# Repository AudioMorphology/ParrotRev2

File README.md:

# Parrot

##  Overview

Parrot is a 12hp Eurorack digital delay powered by a Raspberry Pi Pico microcontroller.

The objective is to provide a CD-Quality audio delay  / reverb effect, with a reasonably 
low BOM count

It utilises an 8Mb x 8-Bit (64mBit) PSRAM Memory chip (the AP6404L), and the whole of
this is treated as a 2Mb x 32-Bit audio buffer. This means that we can wrap the read and 
write pointers  with a simple logical &. 

2Mb x 32-Bit is 1Mb at 32-Bit Stereo. At a 48kHz sample rate, this gives a maximum delay 
time of 1,048,576 / 48,000 = 21.84 seconds 

The ADC and DAC ICs communicate over the i2S protocol, which is handled by custom PIO
functions.

They are actually 24-Bit devices with the data being transmitted left-justified in 32-Bit 
frames, so I am rightshifting to get 24-Bit Integers, then converting these to normalised
floats in the range -1.0 to +1.0 then, after processing it does the same in reverse before 
sending the audio data out to the DAC. 

Reading and writing to the PSRAM buffer is double-buffered using DMA calls from the I2S
interface.

It uses two PIO State machines:

PIO0 for SPI
PIO1 for I2S

The ADC and DAC utilises the low-cost and readily-available I2S modules, which have the 
advantages of already including various ancilliary components, which further reduces the
component count and complexity.

## NOTICE

This code incorporates and acknowledges the following:

### rp2040-psram Copyright © 2023 Ian Scott

rp2040-psram is a header-only library, which implements the SPI protocol using the rp2040 PIO
rather than the in-built SPI interface. This gives far better performance for PSRAM SPI peripherals

### i2s Copyright © 2022 Daniel Collins

These functions implement the I2S protocol using the rp2040 PIO. and utilise interrupt-driven
DMA double-buffering for Audio I/O.

### Elements of hardware design Copyright © 2012 Emilie Gillet (emilie.o.gillet@gmail.com)

The input and output buffer circuitry was taken directly from Clouds:
https://github.com/pichenettes/eurorack/tree/master/clouds/hardware_design/pcb

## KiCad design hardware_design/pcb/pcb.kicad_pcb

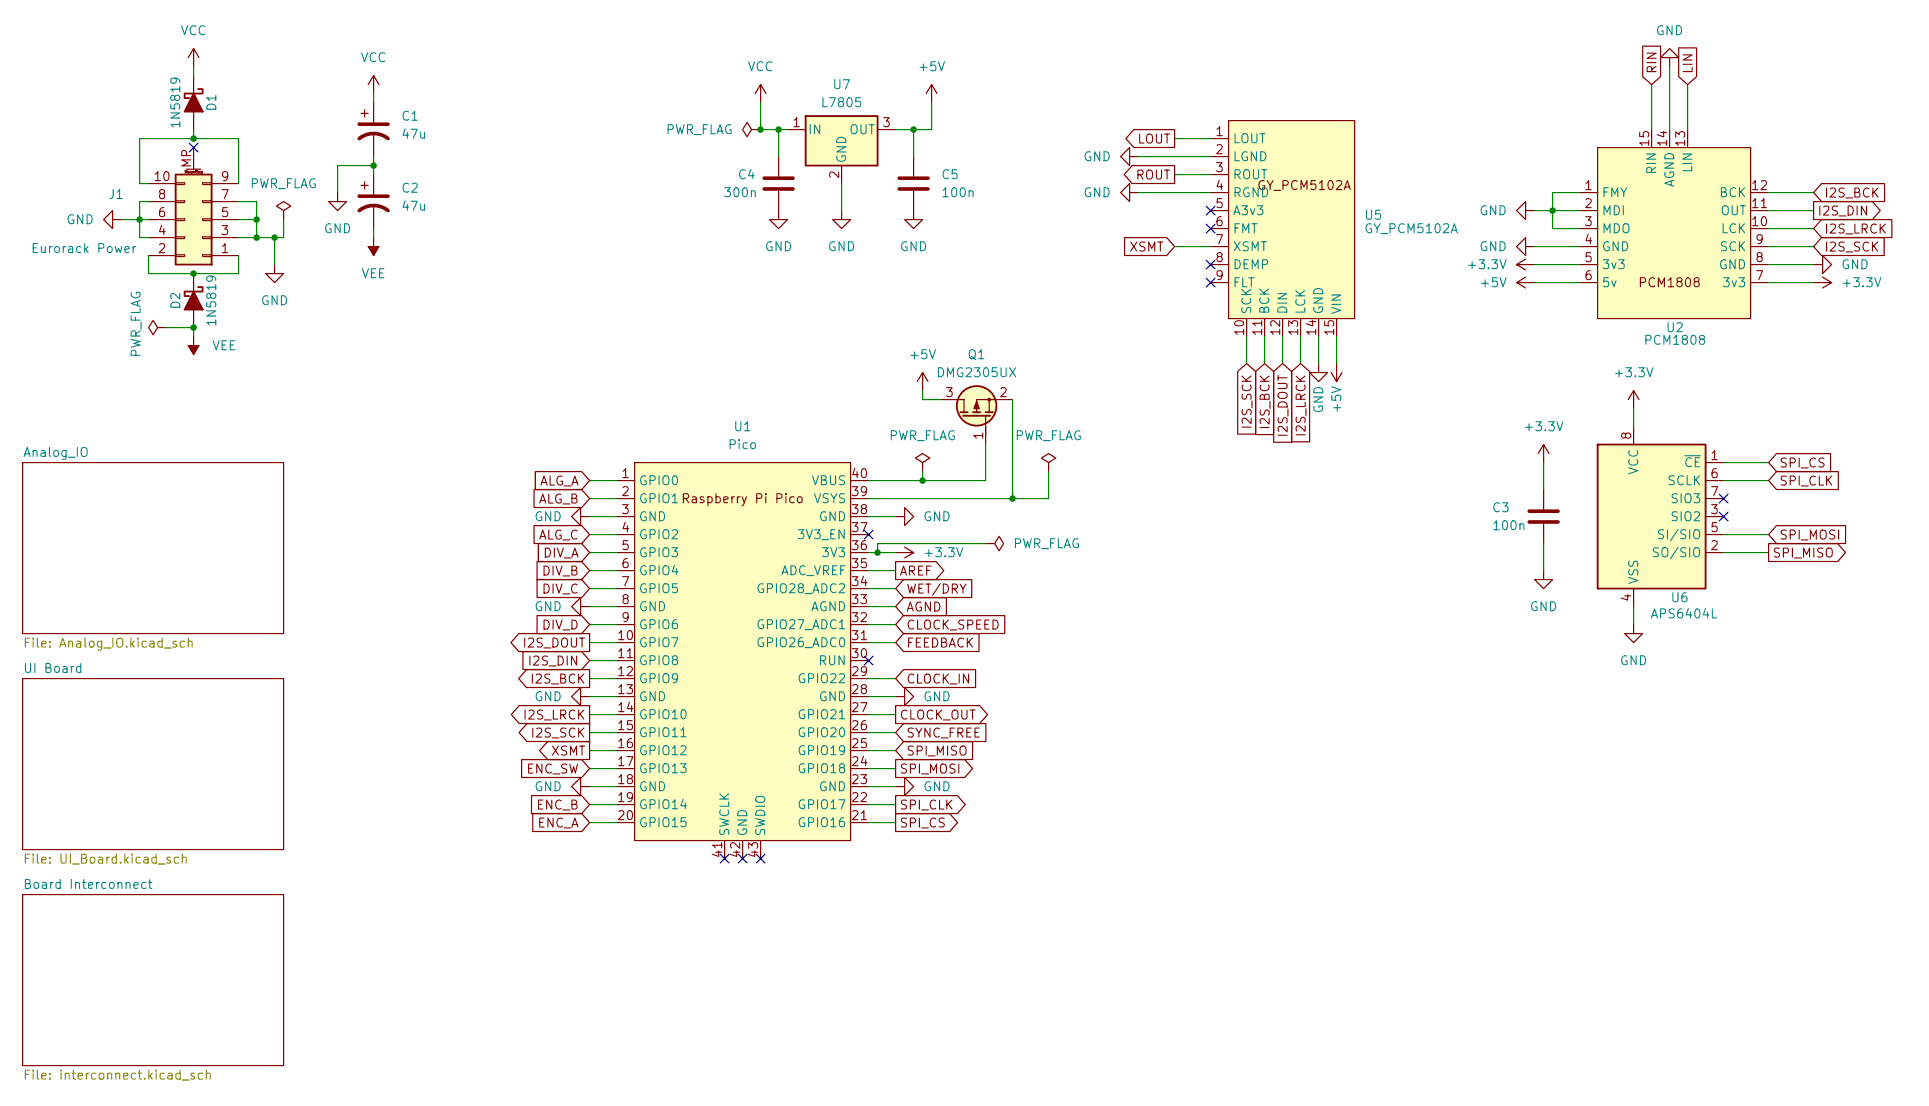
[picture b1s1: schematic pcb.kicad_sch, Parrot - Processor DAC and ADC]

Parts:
C1, C2: 47u; CP_Elec_6.3x5.8
C3, C5: 100n; C_0603_1608Metric
C4: 300n; C_0603_1608Metric
D1, D2: 1N5819; D_DO-41_SOD81_P7.62mm_Horizontal
J1: Eurorack Power; IDC-Header_2x05_P2.54mm_Vertical
Q1: DMG2305UX; SOT-23
U1: Pico; RPi_Pico_SMD_TH
U2: PCM1808
U5: GY_PCM5102A
U6: APS6404L; SOIC-8_3.9x4.9mm_P1.27mm
U7: L7805; TO-252-2 with heatsink

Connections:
+3.3V: C3.1, U1.36 (3V3), U2.5 (3v3), U2.7 (3v3), U6.8 (VCC); also elsewhere on the board
+5V: C5.1, Q1.3 (D), U2.6 (5v), U5.15 (VIN), U7.3 (OUT)
AGND: U1.33 (AGND); also elsewhere on the board
ALG_A: U1.1 (GPIO0); also elsewhere on the board
ALG_B: U1.2 (GPIO1); also elsewhere on the board
ALG_C: U1.4 (GPIO2); also elsewhere on the board
AREF: U1.35 (ADC_VREF); also elsewhere on the board
CLOCK_IN: U1.29 (GPIO22); also elsewhere on the board
CLOCK_OUT: U1.27 (GPIO21); also elsewhere on the board
CLOCK_SPEED: U1.32 (GPIO27_ADC1); also elsewhere on the board
DIV_A: U1.5 (GPIO3); also elsewhere on the board
DIV_B: U1.6 (GPIO4); also elsewhere on the board
DIV_C: U1.7 (GPIO5); also elsewhere on the board
DIV_D: U1.9 (GPIO6); also elsewhere on the board
ENC_A: U1.20 (GPIO15); also elsewhere on the board
ENC_B: U1.19 (GPIO14); also elsewhere on the board
ENC_SW: U1.17 (GPIO13); also elsewhere on the board
FEEDBACK: U1.31 (GPIO26_ADC0); also elsewhere on the board
GND: C1.2, C2.1, C3.2, C4.2, C5.2, J1.3, J1.4, J1.5, J1.6, J1.7, J1.8, U1.3 (GND), U1.8 (GND), U1.13 (GND), U1.18 (GND), U1.23 (GND), U1.28 (GND), U1.38 (GND), U2.1 (FMY), U2.2 (MDI), U2.3 (MDO), U2.4 (GND), U2.8 (GND), U2.14 (AGND), U5.2 (LGND), U5.4 (RGND), U5.14 (GND), U6.4 (VSS), U7.2 (GND); also elsewhere on the board
I2S_BCK: U1.12 (GPIO9), U2.12 (BCK), U5.11 (BCK)
I2S_DIN: U1.11 (GPIO8), U2.11 (OUT)
I2S_DOUT: U1.10 (GPIO7), U5.12 (DIN)
I2S_LRCK: U1.14 (GPIO10), U2.10 (LCK), U5.13 (LCK)
I2S_SCK: U1.15 (GPIO11), U2.9 (SCK), U5.10 (SCK)
LIN: U2.13 (LIN); also elsewhere on the board
LOUT: U5.1 (LOUT); also elsewhere on the board
unnamed: D1.2 (A), J1.9, J1.10
unnamed: D2.1 (K), J1.1, J1.2
unnamed: Q1.1 (G), U1.40 (VBUS)
unnamed: Q1.2 (S), U1.39 (VSYS)
RIN: U2.15 (RIN); also elsewhere on the board
ROUT: U5.3 (ROUT); also elsewhere on the board
SPI_CLK: U1.22 (GPIO17), U6.6 (SCLK)
SPI_CS: U1.21 (GPIO16), U6.1 (~CE)
SPI_MISO: U1.25 (GPIO19), U6.2 (SO/SIO)
SPI_MOSI: U1.24 (GPIO18), U6.5 (SI/SIO)
SYNC_FREE: U1.26 (GPIO20); also elsewhere on the board
VCC: C1.1, C4.1, D1.1 (K), U7.1 (IN); also elsewhere on the board
VEE: C2.2, D2.2 (A); also elsewhere on the board
WET/DRY: U1.34 (GPIO28_ADC2); also elsewhere on the board
XSMT: U1.16 (GPIO12), U5.7 (XSMT)

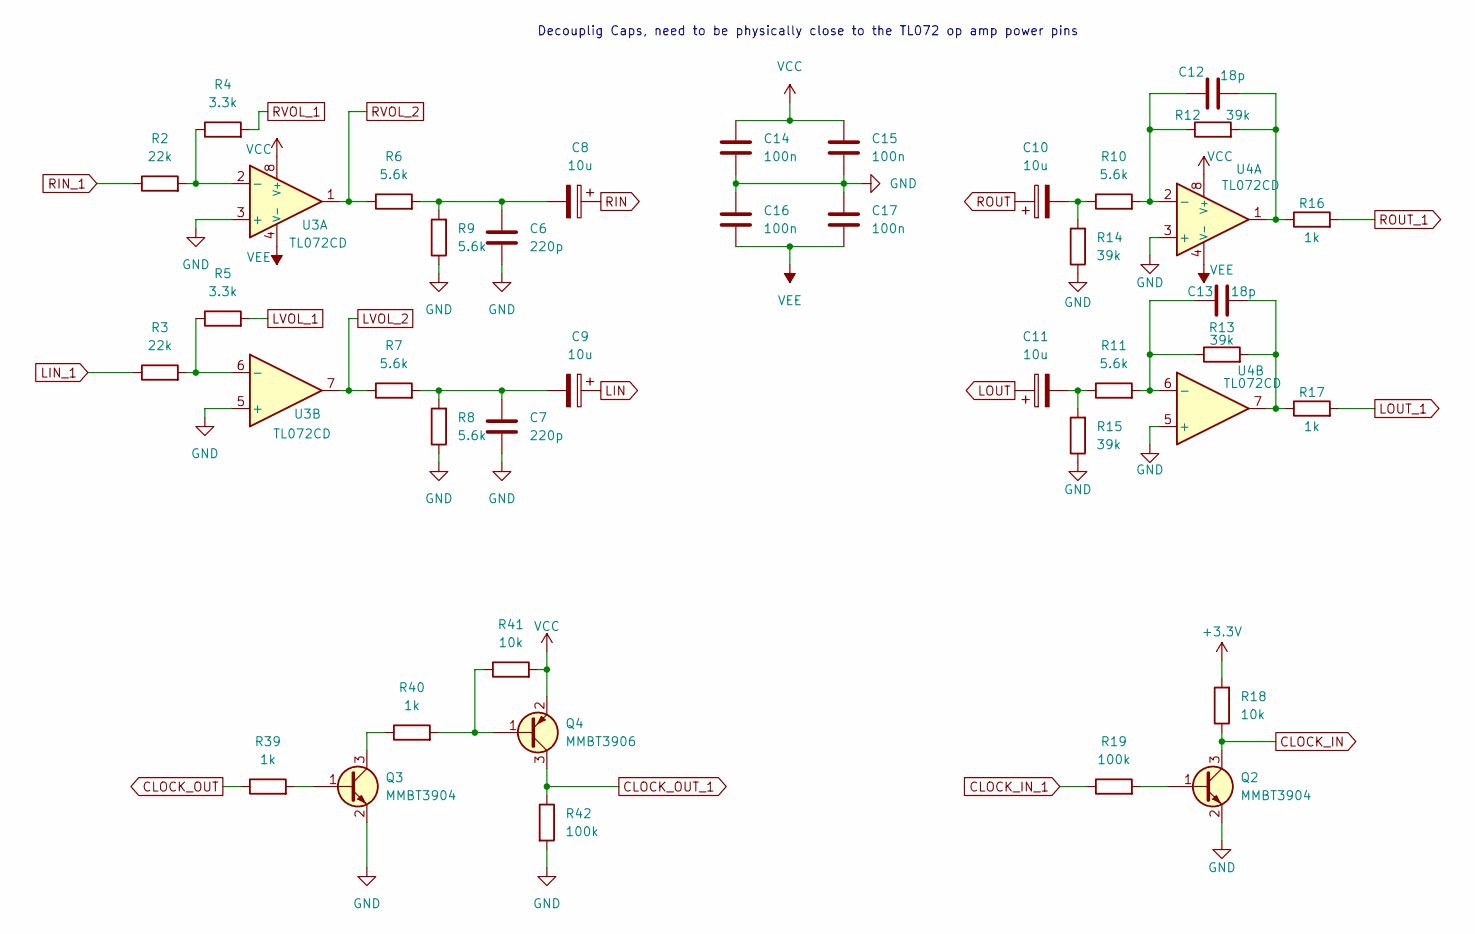
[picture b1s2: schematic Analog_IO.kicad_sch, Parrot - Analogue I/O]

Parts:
C6, C7: 220p; C_0603_1608Metric
C8, C9, C10, C11: 10u; CP_Elec_6.3x5.8
C12, C13: 18p; C_0603_1608Metric
C14, C15, C16, C17: 100n; C_0603_1608Metric
Q2, Q3: MMBT3904; SOT-23
Q4: MMBT3906; SOT-23
R2, R3: 22k; R_0603_1608Metric_Pad1.05x0.95mm_HandSolder
R4, R5: 3.3k; R_0603_1608Metric_Pad1.05x0.95mm_HandSolder
R6, R7, R8, R9, R10, R11: 5.6k; R_0603_1608Metric_Pad1.05x0.95mm_HandSolder
R12, R13, R14, R15: 39k; R_0603_1608Metric_Pad1.05x0.95mm_HandSolder
R16, R17, R39, R40: 1k; R_0603_1608Metric_Pad1.05x0.95mm_HandSolder
R18, R41: 10k; R_0603_1608Metric_Pad1.05x0.95mm_HandSolder
R19, R42: 100k; R_0603_1608Metric_Pad1.05x0.95mm_HandSolder
U3, U4: TL072CD; SO-8_3.9x4.9mm_P1.27mm

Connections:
+3.3V: R18.2; also elsewhere on the board
CLOCK_IN: Q2.3 (C), R18.1; also elsewhere on the board
CLOCK_IN_1: R19.1; also elsewhere on the board
CLOCK_OUT: R39.1; also elsewhere on the board
CLOCK_OUT_1: Q4.3 (C), R42.1; also elsewhere on the board
GND: C6.2, C7.2, C14.2, C15.2, C16.1, C17.1, Q2.2 (E), Q3.2 (E), R8.1, R9.1, R14.1, R15.1, R42.2, U3.3 (+), U3.5 (+), U4.3 (+), U4.5 (+); also elsewhere on the board
LIN: C9.1; also elsewhere on the board
LIN_1: R3.1; also elsewhere on the board
LOUT: C11.1; also elsewhere on the board
LOUT_1: R17.2; also elsewhere on the board
LVOL_1: R5.2; also elsewhere on the board
LVOL_2: R7.1, U3.7; also elsewhere on the board
unnamed: C6.1, C8.2, R6.2, R9.2
unnamed: C7.1, C9.2, R7.2, R8.2
unnamed: C10.2, R10.1, R14.2
unnamed: C11.2, R11.1, R15.2
unnamed: C12.2, R12.2, R16.1, U4.1
unnamed: C13.2, R13.2, R17.1, U4.7
unnamed: Q2.1 (B), R19.2
unnamed: Q3.1 (B), R39.2
unnamed: Q3.3 (C), R40.1
unnamed: Q4.1 (B), R40.2, R41.1
unnamed: R2.2, R4.1, U3.2 (-)
unnamed: R3.2, R5.1, U3.6 (-)
unnamed: C12.1, R10.2, R12.1, U4.2 (-)
unnamed: C13.1, R11.2, R13.1, U4.6 (-)
RIN: C8.1; also elsewhere on the board
RIN_1: R2.1; also elsewhere on the board
ROUT: C10.1; also elsewhere on the board
ROUT_1: R16.2; also elsewhere on the board
RVOL_1: R4.2; also elsewhere on the board
RVOL_2: R6.1, U3.1; also elsewhere on the board
VCC: C14.1, C15.1, Q4.2 (E), R41.2, U3.8 (V+), U4.8 (V+); also elsewhere on the board
VEE: C16.2, C17.2, U3.4 (V-), U4.4 (V-); also elsewhere on the board

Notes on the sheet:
Decouplig Caps, need to be physically close to the TL072 op amp power pins

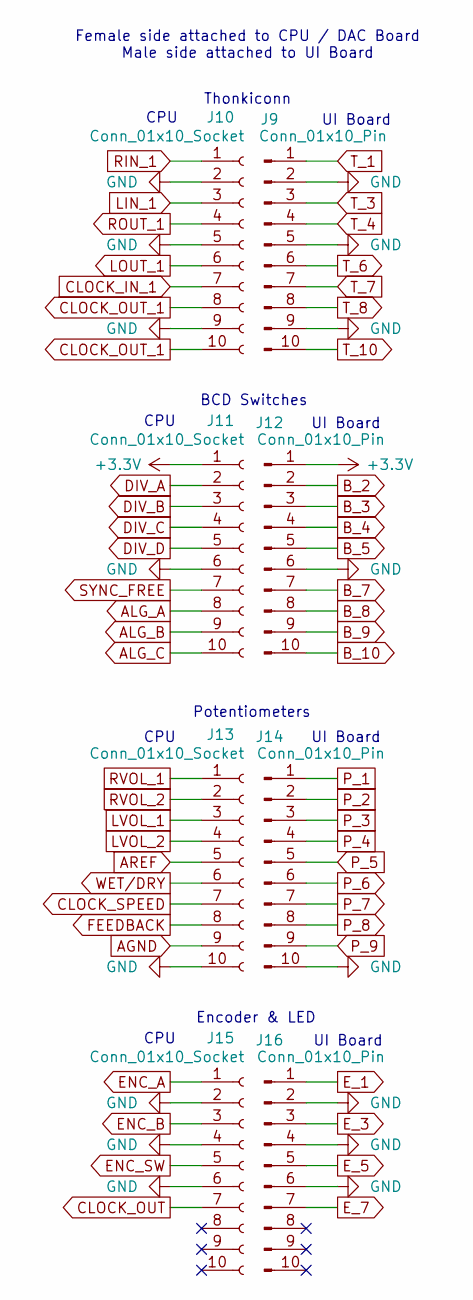
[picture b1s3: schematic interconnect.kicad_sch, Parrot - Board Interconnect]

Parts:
J9, J12, J14, J16: Conn_01x10_Pin; PinHeader_1x10_P2.54mm_Vertical
J10, J11, J13, J15: Conn_01x10_Socket; PinSocket_1x10_P2.54mm_Vertical

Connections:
+3.3V: J11.1, J12.1; also elsewhere on the board
AGND: J13.9; also elsewhere on the board
ALG_A: J11.8; also elsewhere on the board
ALG_B: J11.9; also elsewhere on the board
ALG_C: J11.10; also elsewhere on the board
AREF: J13.5; also elsewhere on the board
B_2: J12.2; also elsewhere on the board
B_3: J12.3; also elsewhere on the board
B_4: J12.4; also elsewhere on the board
B_5: J12.5; also elsewhere on the board
B_7: J12.7; also elsewhere on the board
B_8: J12.8; also elsewhere on the board
B_9: J12.9; also elsewhere on the board
B_10: J12.10; also elsewhere on the board
CLOCK_IN_1: J10.7; also elsewhere on the board
CLOCK_OUT: J15.7; also elsewhere on the board
CLOCK_OUT_1: J10.8, J10.10; also elsewhere on the board
CLOCK_SPEED: J13.7; also elsewhere on the board
DIV_A: J11.2; also elsewhere on the board
DIV_B: J11.3; also elsewhere on the board
DIV_C: J11.4; also elsewhere on the board
DIV_D: J11.5; also elsewhere on the board
ENC_A: J15.1; also elsewhere on the board
ENC_B: J15.3; also elsewhere on the board
ENC_SW: J15.5; also elsewhere on the board
E_1: J16.1; also elsewhere on the board
E_3: J16.3; also elsewhere on the board
E_5: J16.5; also elsewhere on the board
E_7: J16.7; also elsewhere on the board
FEEDBACK: J13.8; also elsewhere on the board
GND: J9.2, J9.5, J9.9, J10.2, J10.5, J10.9, J11.6, J12.6, J13.10, J14.10, J15.2, J15.4, J15.6, J16.2, J16.4, J16.6; also elsewhere on the board
LIN_1: J10.3; also elsewhere on the board
LOUT_1: J10.6; also elsewhere on the board
LVOL_1: J13.3; also elsewhere on the board
LVOL_2: J13.4; also elsewhere on the board
P_1: J14.1; also elsewhere on the board
P_2: J14.2; also elsewhere on the board
P_3: J14.3; also elsewhere on the board
P_4: J14.4; also elsewhere on the board
P_5: J14.5; also elsewhere on the board
P_6: J14.6; also elsewhere on the board
P_7: J14.7; also elsewhere on the board
P_8: J14.8; also elsewhere on the board
P_9: J14.9; also elsewhere on the board
RIN_1: J10.1; also elsewhere on the board
ROUT_1: J10.4; also elsewhere on the board
RVOL_1: J13.1; also elsewhere on the board
RVOL_2: J13.2; also elsewhere on the board
SYNC_FREE: J11.7; also elsewhere on the board
T_1: J9.1; also elsewhere on the board
T_3: J9.3; also elsewhere on the board
T_4: J9.4; also elsewhere on the board
T_6: J9.6; also elsewhere on the board
T_7: J9.7; also elsewhere on the board
T_8: J9.8; also elsewhere on the board
T_10: J9.10; also elsewhere on the board
WET/DRY: J13.6; also elsewhere on the board

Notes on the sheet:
Encoder & LED
UI Board
Potentiometers
CPU
Thonkiconn
BCD Switches
Female side attached to CPU / DAC Board Male side attached to UI Board

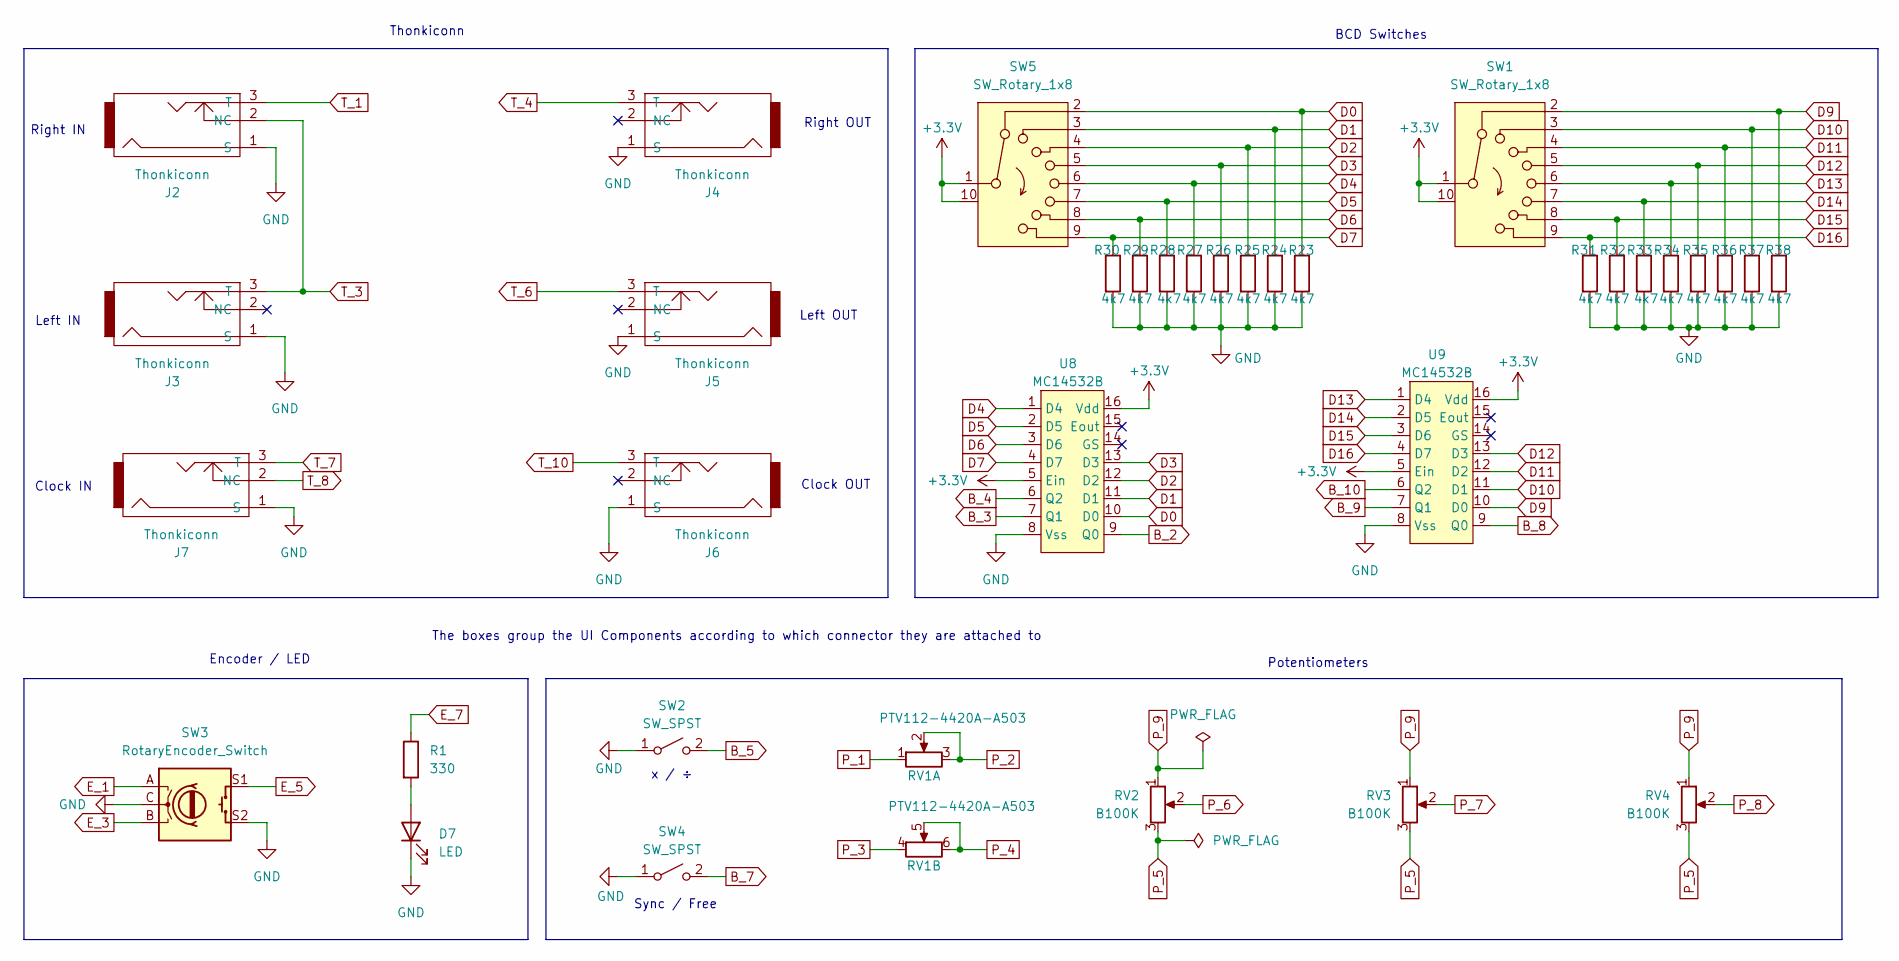
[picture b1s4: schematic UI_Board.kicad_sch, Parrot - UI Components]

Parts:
D7: LED; LED_D3.0mm
J2, J3, J4, J5, J6, J7: Thonkiconn
R1: 330; R_0603_1608Metric_Pad1.05x0.95mm_HandSolder
R23, R24, R25, R26, R27, R28, R29, R30, R31, R32, R33, R34, R35, R36, R37, R38: 4k7; R_0603_1608Metric_Pad1.05x0.95mm_HandSolder
RV1: PTV112-4420A-A503; Potentiometer_Bourns_PTV112-4_Dual_Vertical
RV2, RV3, RV4: B100K; Potentiometer_Alpha_RD901F-40-00D_Single_Vertical_CircularH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
SW1, SW5: SW_Rotary_1x8; ALPS Alpine 8-Way rotary switch SRBV Series
SW2, SW4: SW_SPST; SPDT_Switch
SW3: RotaryEncoder_Switch; RotaryEncoder_Alps_EC11E-Switch_Vertical_H20mm
U8, U9: MC14532B; SOIC-16_3.9x9.9mm_P1.27mm

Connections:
+3.3V: SW1.1, SW1.10, SW5.1, SW5.10, U8.5 (Ein), U8.16 (Vdd), U9.5 (Ein), U9.16 (Vdd); also elsewhere on the board
B_2: U8.9 (Q0); also elsewhere on the board
B_3: U8.7 (Q1); also elsewhere on the board
B_4: U8.6 (Q2); also elsewhere on the board
B_5: SW2.2 (B); also elsewhere on the board
B_7: SW4.2 (B); also elsewhere on the board
B_8: U9.9 (Q0); also elsewhere on the board
B_9: U9.7 (Q1); also elsewhere on the board
B_10: U9.6 (Q2); also elsewhere on the board
D0: R23.1, SW5.2, U8.10 (D0)
D1: R24.1, SW5.3, U8.11 (D1)
D2: R25.1, SW5.4, U8.12 (D2)
D3: R26.1, SW5.5, U8.13 (D3)
D4: R27.1, SW5.6, U8.1 (D4)
D5: R28.1, SW5.7, U8.2 (D5)
D6: R29.1, SW5.8, U8.3 (D6)
D7: R30.1, SW5.9, U8.4 (D7)
D9: R38.1, SW1.2, U9.10 (D0)
D10: R37.1, SW1.3, U9.11 (D1)
D11: R36.1, SW1.4, U9.12 (D2)
D12: R35.1, SW1.5, U9.13 (D3)
D13: R34.1, SW1.6, U9.1 (D4)
D14: R33.1, SW1.7, U9.2 (D5)
D15: R32.1, SW1.8, U9.3 (D6)
D16: R31.1, SW1.9, U9.4 (D7)
E_1: SW3.A; also elsewhere on the board
E_3: SW3.B; also elsewhere on the board
E_5: SW3.S1; also elsewhere on the board
E_7: R1.1; also elsewhere on the board
GND: D7.1 (K), J2.1 (S), J3.1 (S), J4.1 (S), J5.1 (S), J6.1 (S), J7.1 (S), R23.2, R24.2, R25.2, R26.2, R27.2, R28.2, R29.2, R30.2, R31.2, R32.2, R33.2, R34.2, R35.2, R36.2, R37.2, R38.2, SW2.1 (A), SW3.C, SW3.S2, SW4.1 (A), U8.8 (Vss), U9.8 (Vss); also elsewhere on the board
unnamed: D7.2 (A), R1.2
P_1: RV1.1; also elsewhere on the board
P_2: RV1.2, RV1.3; also elsewhere on the board
P_3: RV1.4; also elsewhere on the board
P_4: RV1.5, RV1.6; also elsewhere on the board
P_5: RV2.3, RV3.3, RV4.3; also elsewhere on the board
P_6: RV2.2; also elsewhere on the board
P_7: RV3.2; also elsewhere on the board
P_8: RV4.2; also elsewhere on the board
P_9: RV2.1, RV3.1, RV4.1; also elsewhere on the board
T_1: J2.3 (T); also elsewhere on the board
T_3: J2.2 (NC), J3.3 (T); also elsewhere on the board
T_4: J4.3 (T); also elsewhere on the board
T_6: J5.3 (T); also elsewhere on the board
T_7: J7.3 (T); also elsewhere on the board
T_8: J7.2 (NC); also elsewhere on the board
T_10: J6.3 (T); also elsewhere on the board

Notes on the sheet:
BCD Switches
Clock OUT
The boxes group the UI Components according to which connector they are attached to
Potentiometers
Encoder / LED
Clock IN
Thonkiconn
x / ÷
Sync / Free
Right IN
Right OUT
Left IN
Left OUT

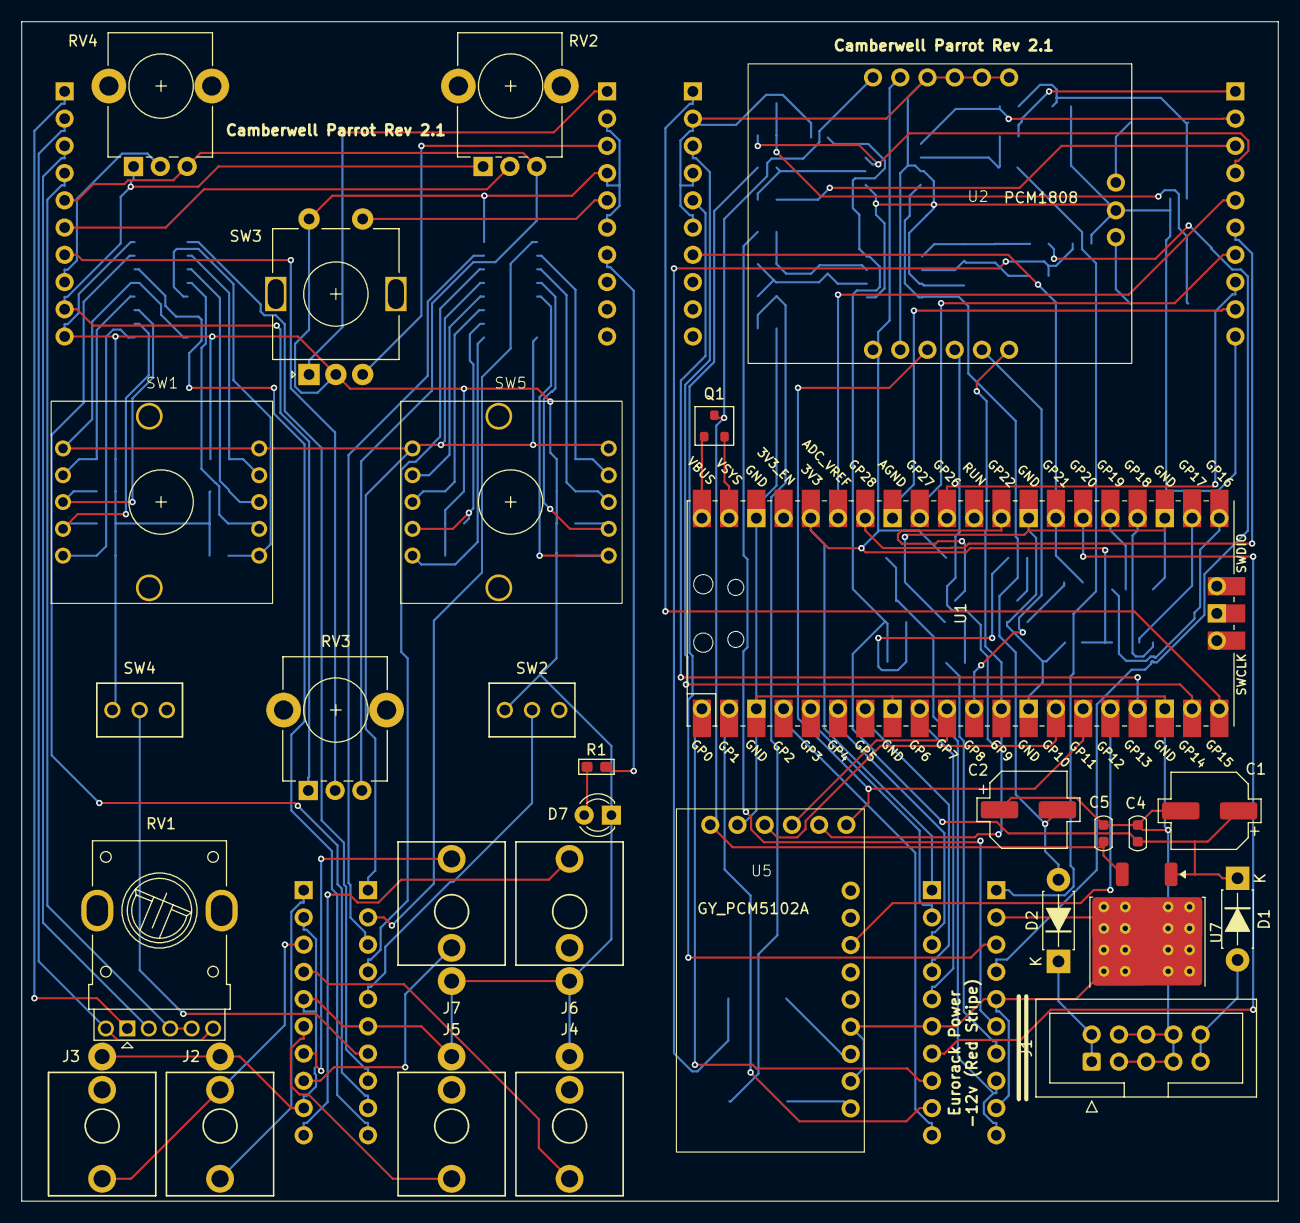
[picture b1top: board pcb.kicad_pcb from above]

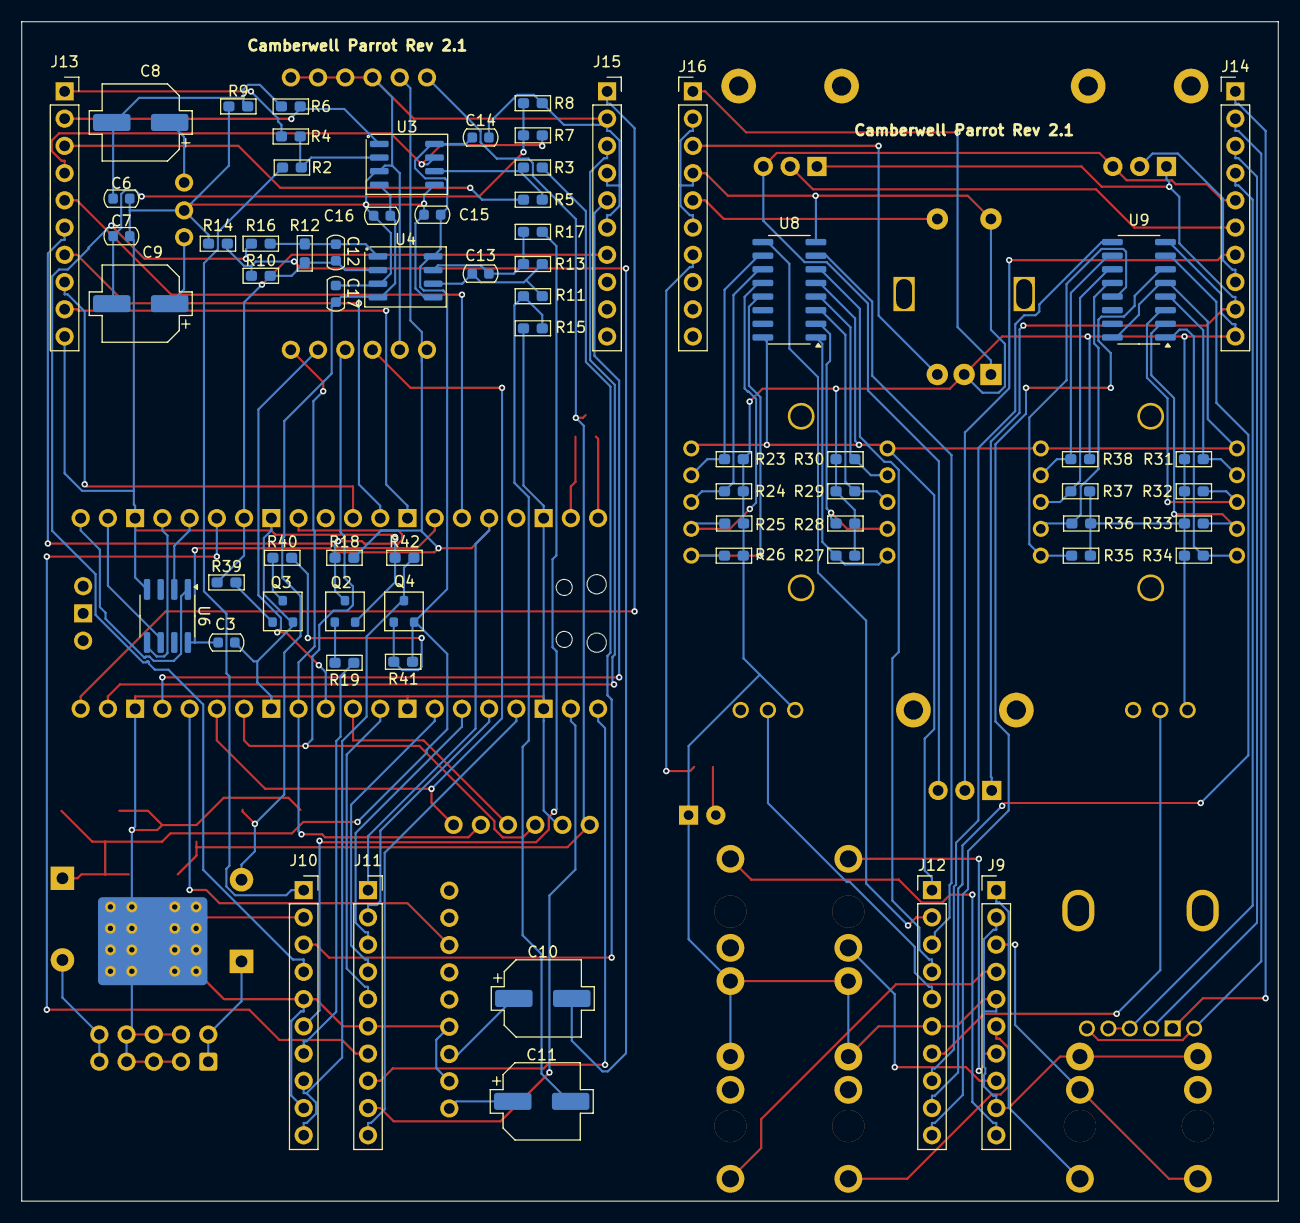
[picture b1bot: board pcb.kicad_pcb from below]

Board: 2 copper layers, 117.2 x 110.0 mm, 96 parts (67 on the bottom side), 110 nets.

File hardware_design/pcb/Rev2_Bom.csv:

"Reference","Value","Datasheet","Footprint","Qty","DNP"
"C1,C2","47u","~","Capacitor_SMD_AKL:CP_Elec_6.3x5.8","2",""
"C3,C5,C14,C15,C16,C17","100n","~","Capacitor_SMD_AKL:C_0603_1608Metric","6",""
"C4","300n","~","Capacitor_SMD_AKL:C_0603_1608Metric","1",""
"C6,C7","220p","~","Capacitor_SMD_AKL:C_0603_1608Metric","2",""
"C8,C9,C10,C11","10u","~","Capacitor_SMD_AKL:CP_Elec_6.3x5.8","4",""
"C12,C13","18p","~","Capacitor_SMD_AKL:C_0603_1608Metric","2",""
"D1,D2","1N5819","https://www.tme.eu/Document/1dcb17797cd83f32e896ece3030f14cc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","Diode_THT_AKL:D_DO-41_SOD81_P7.62mm_Horizontal","2",""
"D7","LED","~","LED_THT:LED_D3.0mm","1",""
"J1","Eurorack Power","~","Connector_IDC:IDC-Header_2x05_P2.54mm_Vertical","1",""
"J2,J3,J4,J5,J6,J7","Thonkiconn","","Eurorack:Thonkiconn","6",""
"J9,J12,J14,J16","Conn_01x10_Pin","~","Connector_PinHeader_2.54mm:PinHeader_1x10_P2.54mm_Vertical","4",""
"J10,J11,J13,J15","Conn_01x10_Socket","~","Connector_PinSocket_2.54mm:PinSocket_1x10_P2.54mm_Vertical","4",""
"Q1","DMG2305UX","https://www.tme.eu/Document/79cbea1ac95301c813f57d9a7787c43d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","Package_TO_SOT_SMD_AKL:SOT-23","1",""
"Q2,Q3","MMBT3904","https://www.tme.eu/Document/12bff749841e3a356e683e9a8e7e4119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","Package_TO_SOT_SMD_AKL:SOT-23","2",""
"Q4","MMBT3906","https://www.tme.eu/Document/1d69ece8147fa5a64114d103f531c790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","Package_TO_SOT_SMD_AKL:SOT-23","1",""
"R1","330","~","Resistor_SMD_AKL:R_0603_1608Metric_Pad1.05x0.95mm_HandSolder","1",""
"R2,R3","22k","~","Resistor_SMD_AKL:R_0603_1608Metric_Pad1.05x0.95mm_HandSolder","2",""
"R4,R5","3.3k","~","Resistor_SMD_AKL:R_0603_1608Metric_Pad1.05x0.95mm_HandSolder","2",""
"R6,R7,R8,R9,R10,R11","5.6k","~","Resistor_SMD_AKL:R_0603_1608Metric_Pad1.05x0.95mm_HandSolder","6",""
"R12,R13,R14,R15","39k","~","Resistor_SMD_AKL:R_0603_1608Metric_Pad1.05x0.95mm_HandSolder","4",""
"R16,R17,R39,R40","1k","~","Resistor_SMD_AKL:R_0603_1608Metric_Pad1.05x0.95mm_HandSolder","4",""
"R18,R41","10k","~","Resistor_SMD_AKL:R_0603_1608Metric_Pad1.05x0.95mm_HandSolder","2",""
"R19,R42","100k","~","Resistor_SMD_AKL:R_0603_1608Metric_Pad1.05x0.95mm_HandSolder","2",""
"R23,R24,R25,R26,R27,R28,R29,R30,R31,R32,R33,R34,R35,R36,R37,R38","4k7","~","Resistor_SMD_AKL:R_0603_1608Metric_Pad1.05x0.95mm_HandSolder","16",""
"RV1","PTV112-4420A-A503","~","DSP_CodecBoards:Potentiometer_Bourns_PTV112-4_Dual_Vertical","1",""
"RV2,RV3,RV4","B100K","~","DSP_CodecBoards:Potentiometer_Alpha_RD901F-40-00D_Single_Vertical_CircularHoles","3",""
"SW1,SW5","SW_Rotary_1x8","~","DSP_CodecBoards:ALPS Alpine 8-Way rotary switch SRBV Series","2",""
"SW2,SW4","SW_SPST","~","europi:SPDT_Switch","2",""
"SW3","RotaryEncoder_Switch","~","DSP_CodecBoards:RotaryEncoder_Alps_EC11E-Switch_Vertical_H20mm","1",""
"U1","Pico","","MCU_RaspberryPi_and_Boards:RPi_Pico_SMD_TH","1",""
"U2","PCM1808","","DSP_CodecBoards:PCM1808","1",""
"U3,U4","TL072CD","https://www.ti.com/lit/ds/symlink/tl072h.pdf?ts=1635057479364","Package_SO_AKL:SO-8_3.9x4.9mm_P1.27mm","2",""
"U5","GY_PCM5102A","","DSP_CodecBoards:GY_PCM5102A","1",""
"U6","APS6404L","https://www.espressif.com/sites/default/files/documentation/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","Package_SO:SOIC-8_3.9x4.9mm_P1.27mm","1",""
"U7","L7805","http://www.st.com/content/ccc/resource/technical/document/da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","DSP_CodecBoards:TO-252-2 with heatsink","1",""
"U8,U9","MC14532B","","Package_SO:SOIC-16_3.9x9.9mm_P1.27mm","2",""

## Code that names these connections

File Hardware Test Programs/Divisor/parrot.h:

/******************************************************************************

parrot

Copyright © 2024 Richard R. Goodwin / Audio Morphology Ltd.

Permission is hereby granted, free of charge, to any person obtaining a copy of
this software and associated documentation files (the “Software”), to deal in
the Software without restriction, including without limitation the rights to
use, copy, modify, merge, publish, distribute, sublicense, and/or sell copies
of the Software, and to permit persons to whom the Software is furnished to do
so, subject to the following conditions:

The above copyright notice and this permission notice shall be included in all
copies or substantial portions of the Software.

THE SOFTWARE IS PROVIDED “AS IS”, WITHOUT WARRANTY OF ANY KIND, EXPRESS OR
IMPLIED, INCLUDING BUT NOT LIMITED TO THE WARRANTIES OF MERCHANTABILITY,
FITNESS FOR A PARTICULAR PURPOSE AND NONINFRINGEMENT. IN NO EVENT SHALL THE
AUTHORS OR COPYRIGHT HOLDERS BE LIABLE FOR ANY CLAIM, DAMAGES OR OTHER
LIABILITY, WHETHER IN AN ACTION OF CONTRACT, TORT OR OTHERWISE, ARISING FROM,
OUT OF OR IN CONNECTION WITH THE SOFTWARE OR THE USE OR OTHER DEALINGS IN THE
SOFTWARE.

******************************************************************************/
/**
 * @file parrot.h
 * 
 * Header file - constant definitions, function prototypes etc
 */
#ifndef PARROT_H
#define PARROT_H

// GPIO Pin definitions
static const uint ALGORITHM_0 = 0;              // LSB of Algorithm 8-Way BCD Switch    Physical Pin 1
static const uint ALGORITHM_1 = 1;              // MSB of Algorithm 8-Way BCD Switch    Physical Pin 2
static const uint ALGORITHM_2 = 2;              // MSB of Algorithm 8-Way BCD Switch    Physical Pin 4
static const uint DIVISOR_0 = 3;                // 8-Way BCD switch-A                   Physical Pin 5
static const uint DIVISOR_1 = 4;                // 8-Way BCD switch-B                   Physical Pin 6
static const uint DIVISOR_2 = 5;                // 8-Way BCD switch-C                   Physical Pin 7
static const uint DIVISOR_3 = 6;                // Mul/Div switch provides 4th Bit      Physical Pin 9
static const uint I2S_DOUT = 7;                 // I2S Data Out                         Physical Pin 10
static const uint I2S_DIN = 8;                  // I2S Data In                          Physical Pin 11
static const uint I2S_BCK = 9;                  // I2S Bit Clock                        Physical Pin 12
static const uint I2S_LRCK = 10;                // I2S Left-Right Clock                 Physical Pin 14
static const uint I2S_SCK = 11;                 // I2S System Clock                     Physical Pin 15
static const uint XSMT_PIN = 12;                // PCM5102 Soft-mute                    Physical Pin 16 
static const uint ENCODER_SW = 13;              // Rotary Encoder switch                Physical pin 17
static const uint ENCODERA_IN = 14;             // Rotary encoder A-leg                 physical pin 19 
static const uint ENCODERB_IN = 15;             // Rotary encoder B-leg                 physical pin 20
static const uint SPI_CS=16;                    // Set in CMakeLists as PSRAM_PIN_CS    Physical Pin 21 
static const uint SPI_SCK=17;                   // Set in CMakeLists as PSRAM_PIN_SCK   Physical Pin 22
static const uint SPI_MOSI=18;                  // Set in CMakeLists as PSRAM_PIN_MOSI  Physical Pin 24
static const uint SPI_MISO=19;                  // Set in CMakeLists as PSRAM_PIN_MISO  Physical Pin 25
static const uint SYNC_FREE = 20;               // Delay sync'd to clock                Physical pin 26
static const uint CLOCK_OUT = 21;               // Internal clock out                   Physical pin 27
static const uint CLOCK_IN = 22;                // External clock in                    Physical pin 29
static const uint POWERSAVE_PIN = 23;           // Set high turns on PWM mode the internal 3v3 regulator, which reduces noise 
static const uint VBUS_SENSE = 24;              // High if VBUS is present, low otherwise
static const uint ONBOARD_LED = 25;             // On-Board LED
static const uint FEEDBACK_PIN = 26;            // feedback amount                      Physical pin 31 (ADC0 Input)
static const uint CLOCKSPEED_PIN = 27;          // Clock Speed                          Physical pin 32 (ADC1 Input)
static const uint WETDRY_PIN = 28;              // Wet/Dry control                      Physical pin 34 (ADC2 Input)
// ADC Channels
static const uint ADC_feedback = 0;
static const uint ADC_Clock = 1;
static const uint ADC_WetDry = 2; 

// AP 6404L Constants
static const uint8_t AP6404_READ = 0x03;        // Read
static const uint8_t AP6404_FREAD = 0x0B;       // Fast Read
static const uint8_t AP6404_WRITE = 0x02;       // Write
static const uint8_t AP6404_RST_EN = 0x66;      // Reset Enable
static const uint8_t AP6404_RESET = 0x99;       // Reset
static const uint8_t AP6404_WBT = 0xC0;         // Wrap Boundary Toggle  
static const uint8_t AP6404_READID = 0x9F;      // Read ID

// Global Variables defined in parrot_main.c
extern double ClockBPM;            // BPM Value for interal clock
extern double ClockFreq;           // Internal Clock Frequency
extern double ClockPeriod;         // Internal Clock Period
extern uint32_t ReadPointer; 
extern uint32_t WritePointer;
extern float glbFeedback;

// function prototypes - parrot_func.c

#endif

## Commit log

2024-12-28 Initial commit of Rev2
2024-12-28 Added hardware test-harness programs
2024-12-29 Rev 2 schematic & circuit board
2025-01-14 Software switch de-bounce added as a result of Rev 2 testing.
2025-01-14 Final Rev 2 hardware checks, adjusting the sync/free settings so that when switched to free-running the glbDelay isn't altered
2025-01-15 Changes to CMakeLists.txt to build and link the latest CMSIS Library. At present this seems to have broken support for the RP2040, so I may just have to live with that fact.
2025-01-21 Rev 2.1 hardware changes
2025-01-22 Experiments with normalisation, plus I changed the way the read and write pointers worked to make it simpler to process the Left and Right channels separately
2025-01-23 Worked through the uint32_t to normalised float conversion by using the audio test harness to print out the binary respresentation
2025-01-30 Integrated gverb into the main Camberwell Parrot codebase on Algorithm Switch G, with Wet/Dry balance and Feedback setting the reverb time
2025-02-04 Added both Gverb and Freeverb algorithms
2025-02-13 Freeverb and Gverb integrated
2025-02-15 First commit of a Euclidean Delay algorithm
2025-02-17 Working on the Euclidean Echoes function
2025-02-17 More changes to Euclidean delay
2025-02-23 23-Feb-2025
